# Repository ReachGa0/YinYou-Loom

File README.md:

# 吟游 Loom

> 基于 FPGA 的纯硬件实时多音色合成电子乐器引擎

---

## 这是什么

**吟游 Loom** 是一套完全运行在国产高云 GW2AR-LV18（Sipeed Tang Nano 20K）FPGA 硬件逻辑中的实时多音色合成电子乐器引擎。

它把音频合成的整条通路 —— 振荡器、包络、混音、输出 —— 全部实现在 HDL 硬件逻辑里，
**没有一行软件参与发声**。所有声音都由 FPGA 根据实时演奏指令**逐音、逐样本**生成，
不包含任何预录 PCM 音频、预置推流或整段录音触发。

交互侧采用"**自研交互语义 + 成品传感器模块 + 板载保底**"的结构：
7 个音名键 + MODE 键负责选音、触发与拨弦；摇杆 X 轴负责 Pitch Bend，
Y 轴同时提供 note-on 力度和持续 expression。超声波与 ADS1115 已取消，
板载 S1/S2 负责音色与效果器切换。

系统内置**测试模式**，可同时输出多路固定频率信号，
使并发振荡器的数量在频谱仪上**直接可观测、可计数**。

---

## 核心指标

| 指标 | 目标值 | 状态 |
|---|---|---|
| 复音数 | **32 路** | 当前位流已由用户实机确认；精确谱峰计数仍待仪器级证据 |
| 端到端延迟 | **≤ 10 ms** | 设计目标 |
| 演奏维度 | Pitch Bend + note-on 力度 / 持续 expression，共 **2 维** | 已实现 |
| 音色数量 | **4 种**，实时切换 | 已实现 |
| 音频采样率 | **48.000 kHz**（精确） | A4 实机确认；仪器级频率偏差待测 |
| 输出接口 | **I2S** → 板载 MAX98357A（DAC+功放） | 已实机出声 |
| 合规性 | 全部音频逐音、逐样本实时生成 | 设计目标 |

> 表中数据除标注"仿真验证"外，均为**设计目标**，随工程推进将通过综合报告与实测数据逐项替换为真实值。
>
> 🎯 **一等奖冲刺（条件触发）**：见 [`docs/01_项目蓝图.md`](docs/01_项目蓝图.md) §2.4 与 [`docs/04_任务拆解.md`](docs/04_任务拆解.md) P4+。v1.0 范围见 [`docs/16_V1范围与输入语义.md`](docs/16_V1范围与输入语义.md)。

---

## 硬件平台

| 项目 | 内容 |
|---|---|
| 开发板 | **Sipeed Tang Nano 20K**（自备板） |
| FPGA 芯片 | 高云 **GW2AR-LV18QN88C8/I7** |
| 逻辑资源 | 20736 LUT4 / 15552 FF / **48 × 18×18 DSP** |
| 时钟资源 | 2 × PLL ｜ 板载 27 MHz 晶振（PIN4）｜ MS5351（25MHz 晶振） |
| 存储资源 | **828K bit BSRAM（46 块）** ｜ **64M bit SDRAM** ｜ **64M bit QSPI Flash** |
| 音频输出 | **板载 MAX98357A I2S DAC+PA**（BCLK=PIN56 / LRCLK=PIN55 / DIN=PIN54 / PA_EN=PIN51）→ J4 小喇叭 |
| 板载外设 | 6 × LED（PIN15-20）｜ 1 × WS2812（PIN79）｜ 2 × 按键（PIN88/PIN87） |
| 工具链 | **Gowin EDA V1.9.11.03 Education**（支持本芯片，无需 license） |

**音频时钟方案**

```
板载 27 MHz 晶振 → rPLL(IDIV=3,FBDIV=8,ODIV=8) → 72.000 MHz
                     ├─ frac_div(8/125) ──> bit_tick 4.608 MHz（长期平均精确）
                     └─ i2s_tx ÷2 ────────> BCLK 2.304 MHz
                                              48 BCLK / 帧 → 48000.000 Hz
```

> **方案演进记录**：
> 1. 原定 100.8MHz 不可行——需分频比 224/15 或 448/15，超出 rPLL 的 FBDIV ≤ 64、IDIV ≤ 64 限制；
> 2. 69.12MHz 在数学上可达，但 `fPFD = 27 ÷ 25 = 1.08MHz`，低于 Gowin 的 3MHz 下限，布局布线必然报错；
> 3. **最终方案**：72MHz，`27 × 8 ÷ 3 = 72`，`fPFD = 9MHz`，VCO = 576MHz，
>    再用 `frac_div` 以 8/125 的比例产生平均 4.608MHz 位节拍，最终长期平均采样率为 **48000.000 Hz**。
>
> 关键公式（来自官方 UG286）：`f_CLKOUT = f_CLKIN × FBDIV / IDIV`，`f_VCO = f_CLKOUT × ODIV`。
> `fPFD = f_CLKIN / IDIV`，必须落在 3~500MHz；**ODIV 不参与输出分频**，只影响 VCO。
>
> ⚠️ Gowin IP Wizard 会自动替换手填的分频参数（它偏好简洁比值），最终参数以
> `fpga/loom/src/gowin_rpll/gowin_rpll.v` 里的 `defparam` 为准，勿再打开向导重新生成。
> 当前已完成综合、布局布线与位流生成；时序报告确认 PLL 输出为 72.000MHz，setup/hold 违例均为 0。

---

## 系统架构

系统分为三层，全部由 HDL 实现：

```
┌─────────────────────────────────────────────────────────────┐
│  交互层  Interaction                                        │
│  ───────────────────────────────────────────────────────    │
│  摇杆 X：Pitch Bend  ｜  摇杆 Y：力度 / expression           │
│  7 音名键 + MODE：选音 / 触发 / 拨弦                         │
│  板载 S1/S2：TONE / FX  ｜  PIN25：R3 测试模式                │
│                         ↓                                   │
│         选音  ｜  触发 / 拨弦  ｜  力度  ｜  音高弯音         │
└─────────────────────────────────────────────────────────────┘
                              ↓
┌─────────────────────────────────────────────────────────────┐
│  合成层  Synthesis                                          │
│  ───────────────────────────────────────────────────────    │
│  每个声部 = 独立相位累加器 + 频率控制字 + ADSR 包络           │
│  波表合成架构  ｜  多声部并行例化（parameter VOICES）         │
│                         ↓                                   │
│              逐样本混音  →  饱和限幅  →  主增益              │
└─────────────────────────────────────────────────────────────┘
                              ↓
┌─────────────────────────────────────────────────────────────┐
│  输出层  Output                                             │
│  ───────────────────────────────────────────────────────    │
│  I2S 发送器（BCLK / LRCLK / SDATA）  →  外部 DAC            │
└─────────────────────────────────────────────────────────────┘
```

**设计要点**

- **每个声部都是完整的独立振荡器** —— 包含独立相位累加器、频率调控与包络控制。
- **复音数是一个可综合的参数** —— 通过声部并行例化获得，而非软件调度，因此可随器件规模伸缩。
- **波表为所有声部共享** —— 大幅降低存储开销，使复音数主要受逻辑资源而非存储资源约束。
- **整条通路为定长流水线** —— 延迟确定、可预测、可测量。
- **板载外设已核实** —— 核心板提供 2 个用户按键、6 个 LED 和 1 颗 WS2812；BSRAM/SDRAM 规格已写入 `docs/10_硬件引脚与资源.md`。

---

## 目录结构

仓库采用**粗粒度**划分。各目录下的文件组织方式在实施过程中逐步确立：

| 目录 | 用途 | 当前状态 |
|---|---|---|
| [`AGENTS.md`](AGENTS.md) | **AI 协作规则**（Cursor / Copilot 自动加载） | 已有 |
| [`docs/`](docs/) | 设计文档、竞赛文档、报告 | 已有 27 份（00–26） |
| [`reference/`](reference/) | 原始赛题资料、官方手册、工具链笔记 | 已有 7 份 PDF + 工具链笔记 |
| `rtl/` | Verilog 源码 —— **作品主体** | 已有 46 个 `*.v` + 1 个头文件，含合成链、TFT UI、RC 摇杆、拨弦、R3 |
| `sim/` | 仿真测试台与脚本 | 已有 30 个 `tb_*.v` + 一键脚本 |
| `tools/` | Python 辅助工具（波表生成、频谱分析等） | 已有 7 个工具 |
| `fpga/` | 高云工程、PLL、引脚约束与实现产物 | 已有 P3/P4/P5A 工程和音色 / 合唱 / OLED 支线工程（`impl/` 不入库） |
| `hw/` | 硬件资料、自研电路原理图 | 待建（P5） |

> 标注"待建"的目录将在对应开发阶段落位，避免过早固化结构。

### docs/ 索引

| 文档 | 内容 |
|---|---|
| [00_赛题资料摘要](docs/00_赛题资料摘要.md) | 竞赛规则、时间节点、平台资源的整理 |
| [01_项目蓝图](docs/01_项目蓝图.md) | 作品定位、架构取舍、里程碑规划 |
| [02_作品名称与简介](docs/02_作品名称与简介.md) | 名称寓意、多版本作品简介 |
| [03_题目要求拆解](docs/03_题目要求拆解.md) | 赛题原文的逐条结构化拆解 |
| [04_任务拆解](docs/04_任务拆解.md) | 阶段划分、任务清单、验收标准 |
| [05_作品简介_500字版](docs/05_作品简介_500字版.md) | 字数受控的简介版本 |
| [06_决策登记与延后策略](docs/06_决策登记与延后策略.md) | 决策清单与可延后性分析 |
| [07_阶段导览_以智能手表为对照](docs/07_阶段导览_以智能手表为对照.md) | 用 STM32 项目经验类比讲解各阶段 |
| [08_AI协作提示词](docs/08_AI协作提示词.md) | 约束 AI 助手协作方式的提示词 |
| [09_函数与常量索引](docs/09_函数与常量索引.md) | 公共常量、函数、RTL 宏速查表 |
| [10_硬件引脚与资源](docs/10_硬件引脚与资源.md) | 引脚、资源、官方例程与工具链速查 |
| [11_采购清单BOM](docs/11_采购清单BOM.md) | 全项目器件型号、规格、价格与搜索关键词 |
| [12_OLED实验记录](docs/12_OLED实验记录.md) | SH1106 屏幕实验：已点亮，完成列偏移、复位与方向校准 |
| [13_产品形态与交互设计](docs/13_产品形态与交互设计.md) | 三圈视觉、两圈触摸、独奏/和弦模式、KEY 编码器、效果器旋钮与参数屏设计 |
| [14_PCB母板接口设计](docs/14_PCB母板接口设计.md) | 模块化母板接口基线；当前暂停 PCB，优先用面包板和杜邦线验证实物 |
| [15_P5网络映射表](docs/15_P5网络映射表.md) | FPGA 引脚、核心板排针、模块接口和网络名的原理图绘制基线 |
| [16_V1范围与输入语义](docs/16_V1范围与输入语义.md) | v1.0 可演示成品范围、评分映射、摇杆 / 超声波 / 按键统一输入语义 |
| [17_P5C超声波设计](docs/17_P5C超声波设计.md) | P5C 测距接口、状态机、错误恢复、仿真计划和回归接入约定 |
| [18_P6演示修复清单](docs/18_P6演示修复清单.md) | P6 演示前的问题清单与修复记录 |
| [19_FPGA工程实践与踩坑记录](docs/19_FPGA工程实践与踩坑记录.md) | 现象→定位→根因→解决→启示（案例 1–25） |
| [20_触摸模块硬件设计与交接](docs/20_触摸模块硬件设计与交接.md) | 触摸前端（后续增量） |
| [21_OLED显示模块设计与交接](docs/21_OLED显示模块设计与交接.md) | 旧 OLED 方案（历史） |
| [22_TFT显示模块设计与交接](docs/22_TFT显示模块设计与交接.md) | 2.4″ ST7789 TFT 屏参、驱动、UI 与接线 |
| [23_PCB载板v0设计与交接](docs/23_PCB载板v0设计与交接.md) | 嘉立创EDA 载板 v0 摆件、铺铜、走线计划 |
| [24_未完成需求清单](docs/24_未完成需求清单.md) | 按简单到复杂排序的剩余工作与优先级 |
| [25_P6集成与验收指南](docs/25_P6集成与验收指南.md) | RTL 路径、R3、硬件装配、延迟与谱峰验收步骤 |
| [26_提交材料检查表](docs/26_提交材料检查表.md) | 源码、报告、视频和实测证据的最终检查 |

---

## 开发环境

| 工具 | 用途 |
|---|---|
| **Gowin EDA**（云源软件） | 综合、布局布线、烧录 |
| **Icarus Verilog** | 功能仿真（`iverilog` / `vvp`） |
| **GTKWave** | 波形查看 |
| **Python 3** | 波表生成、音频分析、工程脚本 |

> 开发环境的具体版本与配置方式将在 `reference/` 中补充记录。

---

## 开发状态

项目处于**早期开发阶段**。整体推进按阶段划分：

- [x] **P0** 开工前置 —— 环境搭建、硬件采购与板级体检完成
- [x] **P1** 仿真基础设施 —— 波表生成、仿真流程、音频分析工具（P1.1–P1.7 完成；P1.8 可选）
- [x] **P2** 单声部音频引擎 —— 振荡器与 ADSR 包络
- [x] **P3** 输出层 —— RTL、综合、布线与上板出声完成；8Ω 2W 喇叭实机确认 A4 / 440 Hz
- [x] **P4** 多声部合成 —— 参数化例化、混音与四声部上板演示完成；当前主工程已扩至 32 声部
- [x] **P5** 交互层 —— 8 键、MODE、TONE/FX、X/Y 摇杆与统一输入语义完成
- [ ] **P6** 测试模式与验证 —— R3 实机启停/多路发声通过；精确谱峰与延迟测量暂缓
- [ ] **P7** 文档与交付 —— 报告、视频、源码整理

### 当前进度快照

> 本节是**进度的事实来源**。每次完成阶段任务后即时更新，避免进度判断依赖记忆。

| 项目 | 状态 |
|---|---|
| 当前阶段 | **P6 测试模式与验证 / E1 已完成**：32 声部当前位流已由用户实机确认；精确谱峰计数仍待仪器 |
| 已完成 | P0–P4、基础 4 声部与 E1 32 声部合成、I2S 出声、8 键 PCB、MODE 四档、TONE 四档、FX 四档 `DRY/CHORUS/DELAY/REVERB`、TFT、拨弦 |
| 已完成 | 摇杆 X/Y RC 链路；新增 3 点中值去尖峰 + 一阶低通；Y 轴拆分为 note-on `velocity` 和持续 `expression` |
| 已完成 | P5D 输入语义闭环；完整演示采用李萨如相位轨迹和右侧菜单，用户反馈刷新优化后改善 |
| 已完成 | R3 测试模式通过 PIN25 切换；当前测试模式扩展到 32 个质数相干频率，仿真可识别 32 个峰 |
| 下一步 | 用户要求暂不开始重做 REVERB；后续按用户指示处理噪声，E2 第三维和 LED 指引仍待做 |
| 验证 | 全量仿真 **51/51 PASS**，含 REVERB 诊断测试。仿真通过不代表实机混响正常 |
| 综合 | 完整演示 `lissajous_demo`：Logic **12620/20736**、Register **7048/15750**、BSRAM **33/46**、DSP **21/24**；setup/hold **0/0 违例** |
| 位流 | `fpga/lissajous_demo/impl/pnr/lissajous_demo.fs`；SHA256 `91AA94E95F9F1CA5502001BE7954792C43034336A17CF7D406249D098A9B0371`；User Code `0x0000EEBA`。外部 Flash 写入和校验成功，断电后自动加载待明确确认 |
| 硬件状态 | 32 声部、DRY / CHORUS / DELAY 已有实机通过记录；当前 REVERB 首音后有持续撕裂噪声，根因未确定 |
| 载板状态 | 摆件和内层铺铜已有记录，但旧器件表仍含超声波/四键；**接口整改前禁止按旧计划走线**（详见 `docs/23` §8） |
| 进阶缺口 | E2 第 3 维、滑音/扫弦 ❌；E3 ≤5ms、确定性抖动和完整视觉 ❌；E4 ❌ |
| 已确认决策 | E1 32 复音；8 键输入；MODE 四档；TONE 四档；FX=`DRY/CHORUS/DELAY/REVERB`；X=Pitch Bend、Y=力度/expression；取消超声波和 ADS1115；PIN25=R3 |
| 截止时间 | **2026-11-04 18:00** |

---

## 参赛信息

| 项目 | 内容 |
|---|---|
| 竞赛 | 2026 全国大学生嵌入式芯片与系统设计竞赛 |
| 赛道 | FPGA 创新设计赛道 |
| 命题企业 | 广东高云半导体科技股份有限公司 |
| 选题 | 选题二：基于 FPGA 的实时多音色合成电子乐器引擎 |

---

## 许可

本项目源码计划开源，供竞赛评审现场审查音频生成通路。
具体许可协议待补充。

---

## 致谢

本项目所依据的《2026 FPGA 创新设计赛道选题指南》与竞赛通知，
版权归广东高云半导体科技股份有限公司与中国电子教育学会所有，
原始文件存放于 [`reference/`](reference/) 目录，仅供学习参考。

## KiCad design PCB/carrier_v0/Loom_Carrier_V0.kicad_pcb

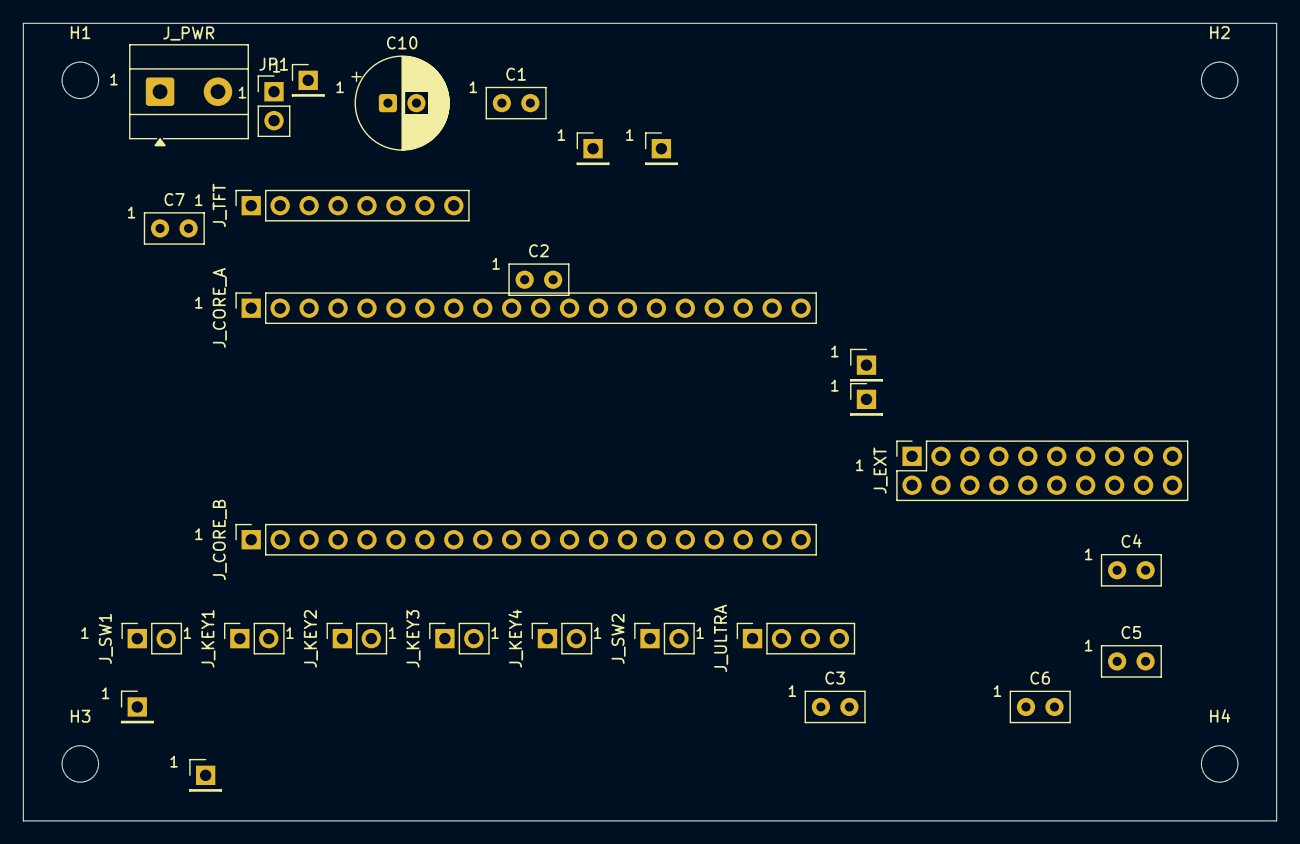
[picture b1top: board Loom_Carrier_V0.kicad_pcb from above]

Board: 4 copper layers, 110.0 x 70.0 mm, 32 parts (0 on the bottom side), 27 nets, no tracks yet.

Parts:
C1, C2, C3, C4, C5, C6, C7: 100n; C_Disc_D5.0mm_W2.5mm_P2.50mm
C10: 100uF; CP_Radial_D8.0mm_P2.50mm
H1, H2, H3, H4: MountingHole_3.2mm_M3
JP1: 5V SEL; PinHeader_1x02_P2.54mm_Vertical
J_CORE_A: CORE A; PinSocket_1x20_P2.54mm_Vertical
J_CORE_B: CORE B; PinSocket_1x20_P2.54mm_Vertical
J_EXT: J_EXT 2x10; PinSocket_2x10_P2.54mm_Vertical
J_KEY1: KEY C4; PinSocket_1x02_P2.54mm_Vertical
J_KEY2: KEY E4; PinSocket_1x02_P2.54mm_Vertical
J_KEY3: KEY G4; PinSocket_1x02_P2.54mm_Vertical
J_KEY4: KEY B4; PinSocket_1x02_P2.54mm_Vertical
J_PWR: 5V IN; TerminalBlock_MetzConnect_Type101_RT01602HBWC_1x02_P5.08mm_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
J_SW1: SW MODE; PinSocket_1x02_P2.54mm_Vertical
J_SW2: SW HI/LO; PinSocket_1x02_P2.54mm_Vertical
J_TFT: TFT ST7789; PinSocket_1x08_P2.54mm_Vertical
J_ULTRA: ULTRA; PinSocket_1x04_P2.54mm_Vertical
TP1: TP1; PinHeader_1x01_P2.54mm_Vertical
TP2: TP2; PinHeader_1x01_P2.54mm_Vertical
TP3: TP3; PinHeader_1x01_P2.54mm_Vertical
TP4: TP4; PinHeader_1x01_P2.54mm_Vertical
TP5: TP5; PinHeader_1x01_P2.54mm_Vertical
TP6: TP6; PinHeader_1x01_P2.54mm_Vertical
TP7: TP7; PinHeader_1x01_P2.54mm_Vertical

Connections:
+3V3: C1.1, C2.1, C3.1, C4.1, C5.1, C6.1, J_CORE_A.19, J_CORE_B.16, J_EXT.13, J_EXT.15, J_EXT.17, J_TFT.2, J_ULTRA.1, TP1.1
+5V: JP1.1, J_CORE_B.1
+5V_SEL: C7.1, C10.1, JP1.2, J_EXT.19, J_PWR.1, TP2.1
GND: C1.2, C2.2, C3.2, C4.2, C5.2, C6.2, C7.2, C10.2, J_CORE_A.20, J_CORE_B.2, J_CORE_B.15, J_EXT.1, J_EXT.3, J_EXT.5, J_EXT.7, J_EXT.9, J_EXT.11, J_EXT.20, J_KEY1.2, J_KEY2.2, J_KEY3.2, J_KEY4.2, J_PWR.2, J_SW1.2, J_SW2.2, J_TFT.1, J_ULTRA.4, TP3.1
I2C_SCL: J_CORE_A.5, J_EXT.16, TP6.1
I2C_SDA: J_CORE_A.4, J_EXT.18, TP7.1
KEY1_C4: J_CORE_A.9, J_KEY1.1
KEY2_E4: J_CORE_A.12, J_KEY2.1
KEY3_G4: J_CORE_A.13, J_KEY3.1
KEY4_B4: J_CORE_A.14, J_KEY4.1
KEY_LEVEL: J_CORE_A.10, J_SW2.1
KEY_MODE: J_CORE_A.8, J_SW1.1
SPARE_41: J_CORE_B.6, J_EXT.2
SPARE_42: J_CORE_B.5, J_EXT.4
SPARE_48: J_CORE_B.10, J_EXT.6
SPARE_49: J_CORE_B.12, J_EXT.8
SPARE_52: J_CORE_B.20, J_EXT.10
SPARE_53: J_CORE_B.19, J_EXT.12
SPARE_86: J_CORE_B.13, J_EXT.14
TFT_BLK: J_CORE_B.3, J_TFT.8
TFT_CS: J_CORE_A.1, J_TFT.7, TP5.1
TFT_DC: J_CORE_A.2, J_TFT.6
TFT_MOSI: J_CORE_B.17, J_TFT.4
TFT_RES: J_CORE_A.3, J_TFT.5
TFT_SCLK: J_CORE_B.18, J_TFT.3, TP4.1
ULTRA_ECHO: J_CORE_B.4, J_ULTRA.3
ULTRA_TRIG: J_CORE_A.11, J_ULTRA.2

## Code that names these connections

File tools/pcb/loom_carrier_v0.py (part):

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    dict(ref="J_ULTRA", label="HC-SR04P 超声波", pins=[
        "+3V3", "ULTRA_TRIG", "ULTRA_ECHO", "GND"],
        verified="接口已冻结（docs/17）；实物排针脚序接板前核对"),
    dict(ref="J_KEY1", label="演奏键 C4", pins=["KEY1_C4", "GND"], verified="2 脚开关，无极性"),
    dict(ref="J_KEY2", label="演奏键 E4", pins=["KEY2_E4", "GND"], verified="2 脚开关，无极性"),
    dict(ref="J_KEY3", label="演奏键 G4", pins=["KEY3_G4", "GND"], verified="2 脚开关，无极性"),
    dict(ref="J_KEY4", label="演奏键 B4", pins=["KEY4_B4", "GND"], verified="2 脚开关，无极性"),
    dict(ref="J_SW1", label="模式开关（独奏/和弦）", pins=["KEY_MODE", "GND"], verified="2 脚开关，无极性"),
    dict(ref="J_SW2", label="电平开关（HI/LO）", pins=["KEY_LEVEL", "GND"], verified="2 脚开关，无极性"),
    # 通用扩展排母 2x10：未定用途的引脚全引出来（含 I2C 与全部 SPARE）
    # 注意：PIN76 是 TFT 背光（TFT_BLK），不是备用脚 —— 这里只列真正的 SPARE
    dict(ref="J_EXT", label="通用扩展排母 2x10", pins=[
        "SPARE_41", "SPARE_42", "SPARE_48", "SPARE_49", "SPARE_52",
        "SPARE_53", "SPARE_86", "I2C_SCL", "I2C_SDA", "GND",
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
